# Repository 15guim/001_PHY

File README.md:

# 001PHY
A simple physical protocol that supports low frequency serial communication.

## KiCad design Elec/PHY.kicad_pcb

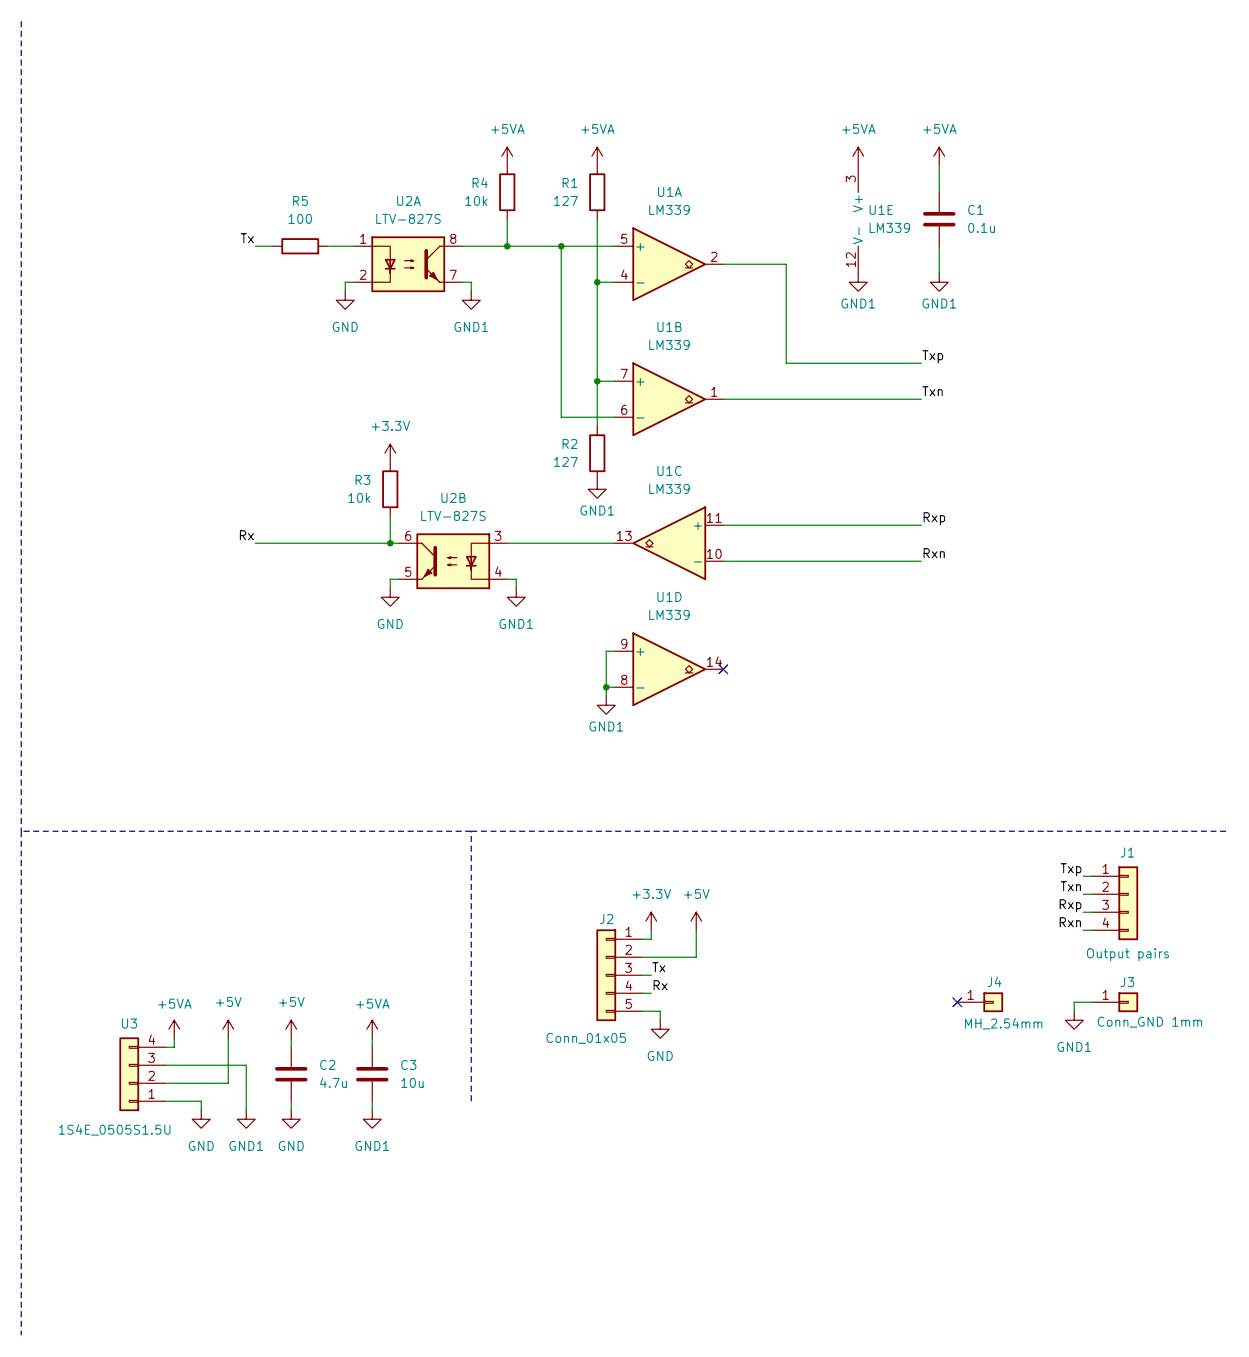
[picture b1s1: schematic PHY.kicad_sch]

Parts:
C1: 0.1u; C_0603_1608Metric
C2: 4.7u; C_0603_1608Metric
C3: 10u; C_0603_1608Metric
J1: Output pairs; PinSocket_1x04_P2.54mm_Vertical_SMD_Pin1Left
J2: Conn_01x05; PinSocket_1x05_P2.54mm_Vertical
J3: Conn_GND 1mm; PinHeader_1x01_P1.27mm_Vertical
J4: MH_2.54mm; PinSocket_1x01_P2.54mm_Vertical
R1, R2: 127; R_0603_1608Metric
R3, R4: 10k; R_0603_1608Metric
R5: 100; R_0603_1608Metric
U1: LM339; TSSOP-14_4.4x5mm_P0.65mm
U2: LTV-827S; SMDIP-8_W9.53mm
U3: 1S4E_0505S1.5U; PinHeader_1x04_P2.54mm_Vertical

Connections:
+3.3V: J2.1, R3.1
+5V: C2.1, J2.2, U3.2
+5VA: C1.1, C3.1, R1.1, R4.1, U1.3 (V+), U3.4
/Rx: J2.4, R3.2, U2.6
/Rxn: J1.4, U1.10 (-)
/Rxp: J1.3, U1.11 (+)
/Tx: J2.3, R5.1
/Txn: J1.2, U1.1
/Txp: J1.1, U1.2
GND: C2.2, J2.5, U2.2, U2.5, U3.1
GND1: C1.2, C3.2, J3.1, R2.2, U1.8 (-), U1.9 (+), U1.12 (V-), U2.4, U2.7, U3.3
unnamed: R5.2, U2.1
unnamed: U1.13, U2.3
unnamed: R4.2, U1.5 (+), U1.6 (-), U2.8
unnamed: R1.2, R2.1, U1.4 (-), U1.7 (+)

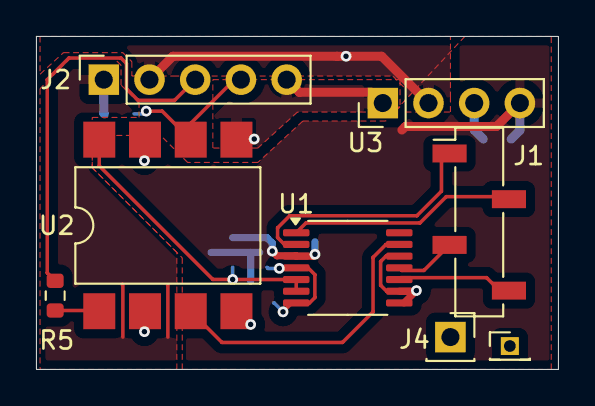
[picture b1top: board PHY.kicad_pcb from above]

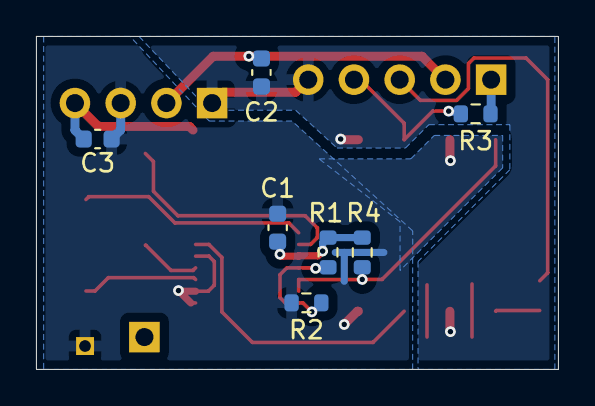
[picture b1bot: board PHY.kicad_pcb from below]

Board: 2 copper layers, 29.0 x 18.5 mm, 15 parts (7 on the bottom side), 15 nets.

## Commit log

2025-02-25 Initial commit
    Getting up to speed...
